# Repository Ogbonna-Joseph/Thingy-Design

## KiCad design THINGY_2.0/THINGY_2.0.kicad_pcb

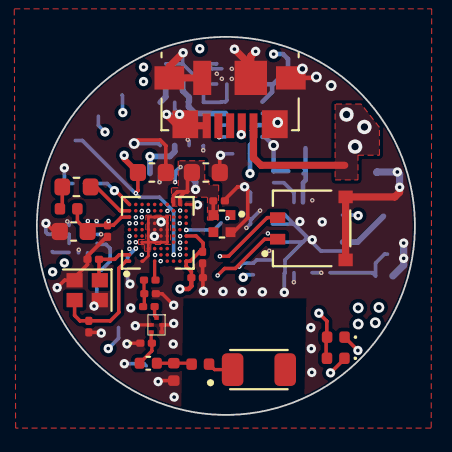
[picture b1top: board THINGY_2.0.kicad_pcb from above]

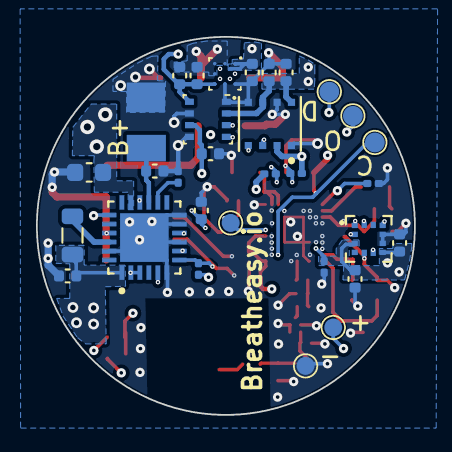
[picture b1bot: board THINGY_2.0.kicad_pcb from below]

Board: 6 copper layers, 21.0 x 21.0 mm, 58 parts (31 on the bottom side), 41 nets.

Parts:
3V0, 3V0#2: 3V0; TestPoint_Pad_D0.9mm
AE1: 2450AT18A100E; ANTC3216X140N
BT1: Battery_Cell; PinSocket_2x01_P2.54mm_Vertical_SMD
C1: 1p; C_0201_0603Metric
C3, C9, C12, C14: 100n; C_0201_0603Metric
C4, C5, C8, C10, C16, C17, C18, C19: 100n; C_0402_1005Metric
C6: 1p; C_0402_1005Metric
C7: 1.0uF; C_0603_1608Metric
C11: 47n; C_0201_0603Metric
C13: 1u; C_0603_1608Metric
C15: 4.7u; C_0603_1608Metric
C20, C21: 8pF; C_0201_0603Metric
C22: 100nF; C_0201_0603Metric
C23: 22uF; C_0402_1005Metric
C24: 2.2uF; C_0603_1608Metric
C25: 1uF; C_0402_1005Metric
C26: 10uF; C_0402_1005Metric
D1: BESDL0201-24; D_0201_0603Metric
D2, D3: LED_Small; LED_0402_1005Metric
FL1: SAFFB2G45MA0F0A
Gnd: Gnd; TestPoint_Pad_D0.9mm
Gnd#2, Gnd#3, Gnd#4: Gnd; TestPoint_Pad_D0.9mm
J1: BM02B-ACHSS-GAN-TF(LF)(SN); JST_BM02B-ACHSS-GAN-TF(LF)(SN)
J3: USB_B_Micro; USB_Micro-B_Molex_47346-0001
L1: 3.9nH; L_0201_0603Metric
L2: 4.7nH; L_0201_0603Metric
L3: 2.7nH; L_0402_1005Metric
L4: 3.9nH; L_0402_1005Metric
L5: 15nH; L_0402_1005Metric
L6: 10uH; L_0603_1608Metric
L7: 2.2uH; L_0805_2012Metric
R1, R2: 4.7K; R_0201_0603Metric
R3, R4: 10k; R_0201_0603Metric
U1: SL6805; SL680555
U2: BMM150; WLCSP-12_1.56x1.56mm_P0.4mm
U3: NRF52840-CKAA-R7; BGA94N35P10X10_360X354X51N
U4: BMA400; XDCR_BMA400
U5: BME280; Bosch_LGA-8_2.5x2.5mm_P0.65mm_ClockwisePinNumbering
U6: BME688; IC_BME688
U7: NPM1100-QDAB-R7; QFN50P400X400X90-25N
Y1: X201632MKB4SI; Crystal_SMD_2016-4Pin_2.0x1.6mm

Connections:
+3V0: 3V0#2.1, C3.1, C4.1, C5.1, C7.1, C8.1, C9.1, C10.1, C12.1, C14.1, C15.1, C16.1, C17.1, C18.1, C19.1, C26.1, L7.1, R1.1, R2.1, R3.2, U1.2 (VDD), U2.A1 (PS), U2.B2 (VDDIO), U2.E5 (VDD), U3.B3 (VDD), U3.B8 (VDD), U3.H10 (VDD), U3.J10 (VDDH), U3.K1 (VDD), U3.K5 (VDD), U4.3 (VDDIO), U4.7 (VDD), U5.2 (CSB), U5.6 (VDDIO), U5.8 (VDD), U6.2 (CSB), U6.6 (VDDIO), U6.8 (VDD), U7.1 (VOUTB)
/ANT: L1.2, U3.E1 (ANT)
/BLE_ANT: AE1.1 (A), L4.1
/BLE_RF: FL1.1, L2.1
/CSB_BMA400: U3.A5 (P0.03/AIN1), U4.10 (~CSB)
/D-: J3.2 (D-), U7.19 (D-)
/DEC: U7.2 (VOUTBSET1), U7.3 (VOUTBSET2), U7.21 (DEC)
/DEC1: C22.1, U3.A10 (DEC1)
/DEC_4/6: C11.1, C13.1, L5.2, U3.A8 (DEC4), U3.C2 (DEC6)
/DRDY_BMM150: U2.D4 (DRDY), U3.J5 (P0.20)
/INT1_BMA400: U3.A3 (P1.11), U4.5 (INT1)
/INT2_BMA400: U3.A4 (P1.13), U4.6 (INT2)
/INT_BMM150: U2.D2 (INT), U3.J4 (P0.21)
/ISET: C23.1, D2.2 (A), D3.2 (A), U7.5 (ISET), U7.16 (VSYS)
/MISO_BMA400: U3.G9 (P1.08), U4.1 (SDO)
/MOSI_BMA400: U3.A7 (P0.30/AIN6), U4.2 (SDX)
/RESET: 3V0.1, U3.K6 (P0.18/~RESET)
/RGB_LED: U1.1 (DIN), U3.J7 (P0.14)
/SCK_BMA400: U3.C8 (P0.31/AIN7), U4.12 (SCX)
/SCL: R2.2, U2.A3 (SCK), U3.D9 (P0.27), U5.4 (SCK), U6.4 (SCK)
/SDA: R1.2, U2.B4 (SDI), U3.C9 (P0.26), U5.3 (SDI), U6.3 (SDI)
/SWDCLK: Gnd#3.3 (1), U3.H2 (SWDCLK)
/SWDIO: Gnd#4.1, U3.J2 (SWDIO)
/SWO: Gnd.2 (1), U3.J3 (P1.00/TRACEDATA0)
/VBAT: BT1.1 (+), C25.1, U7.15 (VBAT)
/npm1100_MODE: R3.1, U3.B4 (P1.10), U7.7 (MODE)
GND: BT1.2 (-), C1.2, C3.2, C4.2, C5.2, C7.2, C8.2, C9.2, C10.2, C11.2, C12.2, C13.2, C14.2, C15.2, C16.2, C17.2, C18.2, C19.2, C20.2, C21.2, C22.2, C23.2, C24.2, C25.2, C26.2, D1.1 (A1), FL1.2, FL1.3, FL1.5, Gnd#2.1, J1.S1 (SHIELD), J1.S2 (SHIELD), J3.5 (GND), J3.6 (Shield), L3.1, R4.2, U1.4 (GND), U2.A5 (CSB), U2.C1 (SDO), U2.C5 (GND), U2.E1 (GND), U2.E3 (GND), U3.B7 (VSS), U3.C1 (VSS_PA), U3.C4 (VSS), U3.D3 (VSS), U3.D4 (VSS), U3.D5 (VSS), U3.D6 (VSS), U3.D7 (VSS), U3.D8 (VSS), U3.E4 (VSS), U3.E5 (VSS), U3.E6 (VSS), U3.E7 (VSS), U3.E8 (VSS), U3.F4 (VSS), U3.F5 (VSS), U3.F6 (VSS), U3.F7 (VSS), U3.F8 (VSS), U3.G4 (VSS), U3.G5 (VSS), U3.G6 (VSS), U3.G7 (VSS), U3.G8 (VSS), U3.J9 (VBUS), U3.K10 (VSS), U4.8 (GNDIO), U4.9 (GND), U5.1 (GND), U5.5 (SDO), U5.7 (GND), U6.1 (GND), U6.5 (SDO), U6.7 (GND), U7.6 (SHPACT), U7.9 (VTERMSET), U7.11 (SHPHLD), U7.12 (ICHG), U7.23 (PVSS), U7.25 (EXP), Y1.2, Y1.4
unnamed: C1.1, L1.1, L2.2
unnamed: C6.1, L3.2, L4.2
unnamed: C6.2, D1.2 (A2), FL1.4
unnamed: D2.1 (K), U7.8 (CHG)
unnamed: D3.1 (K), U7.10 (ERR)
unnamed: L5.1, L6.2
unnamed: J1.1, U3.F1 (P0.09/NFC1)
unnamed: J1.2, U3.E2 (P0.10/NFC2)
unnamed: L6.1, U3.A9 (DCC)
unnamed: C20.1, U3.A1 (XC1), Y1.3
unnamed: C21.1, U3.A2 (XC2), Y1.1
unnamed: R4.1, U7.14 (NTC)
unnamed: L7.2, U7.22 (SW)
VBUS: C24.1, J3.1 (VBUS), U7.17 (VBUS)

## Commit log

2023-09-09 Readme file
2023-09-10 6 layers Design01
